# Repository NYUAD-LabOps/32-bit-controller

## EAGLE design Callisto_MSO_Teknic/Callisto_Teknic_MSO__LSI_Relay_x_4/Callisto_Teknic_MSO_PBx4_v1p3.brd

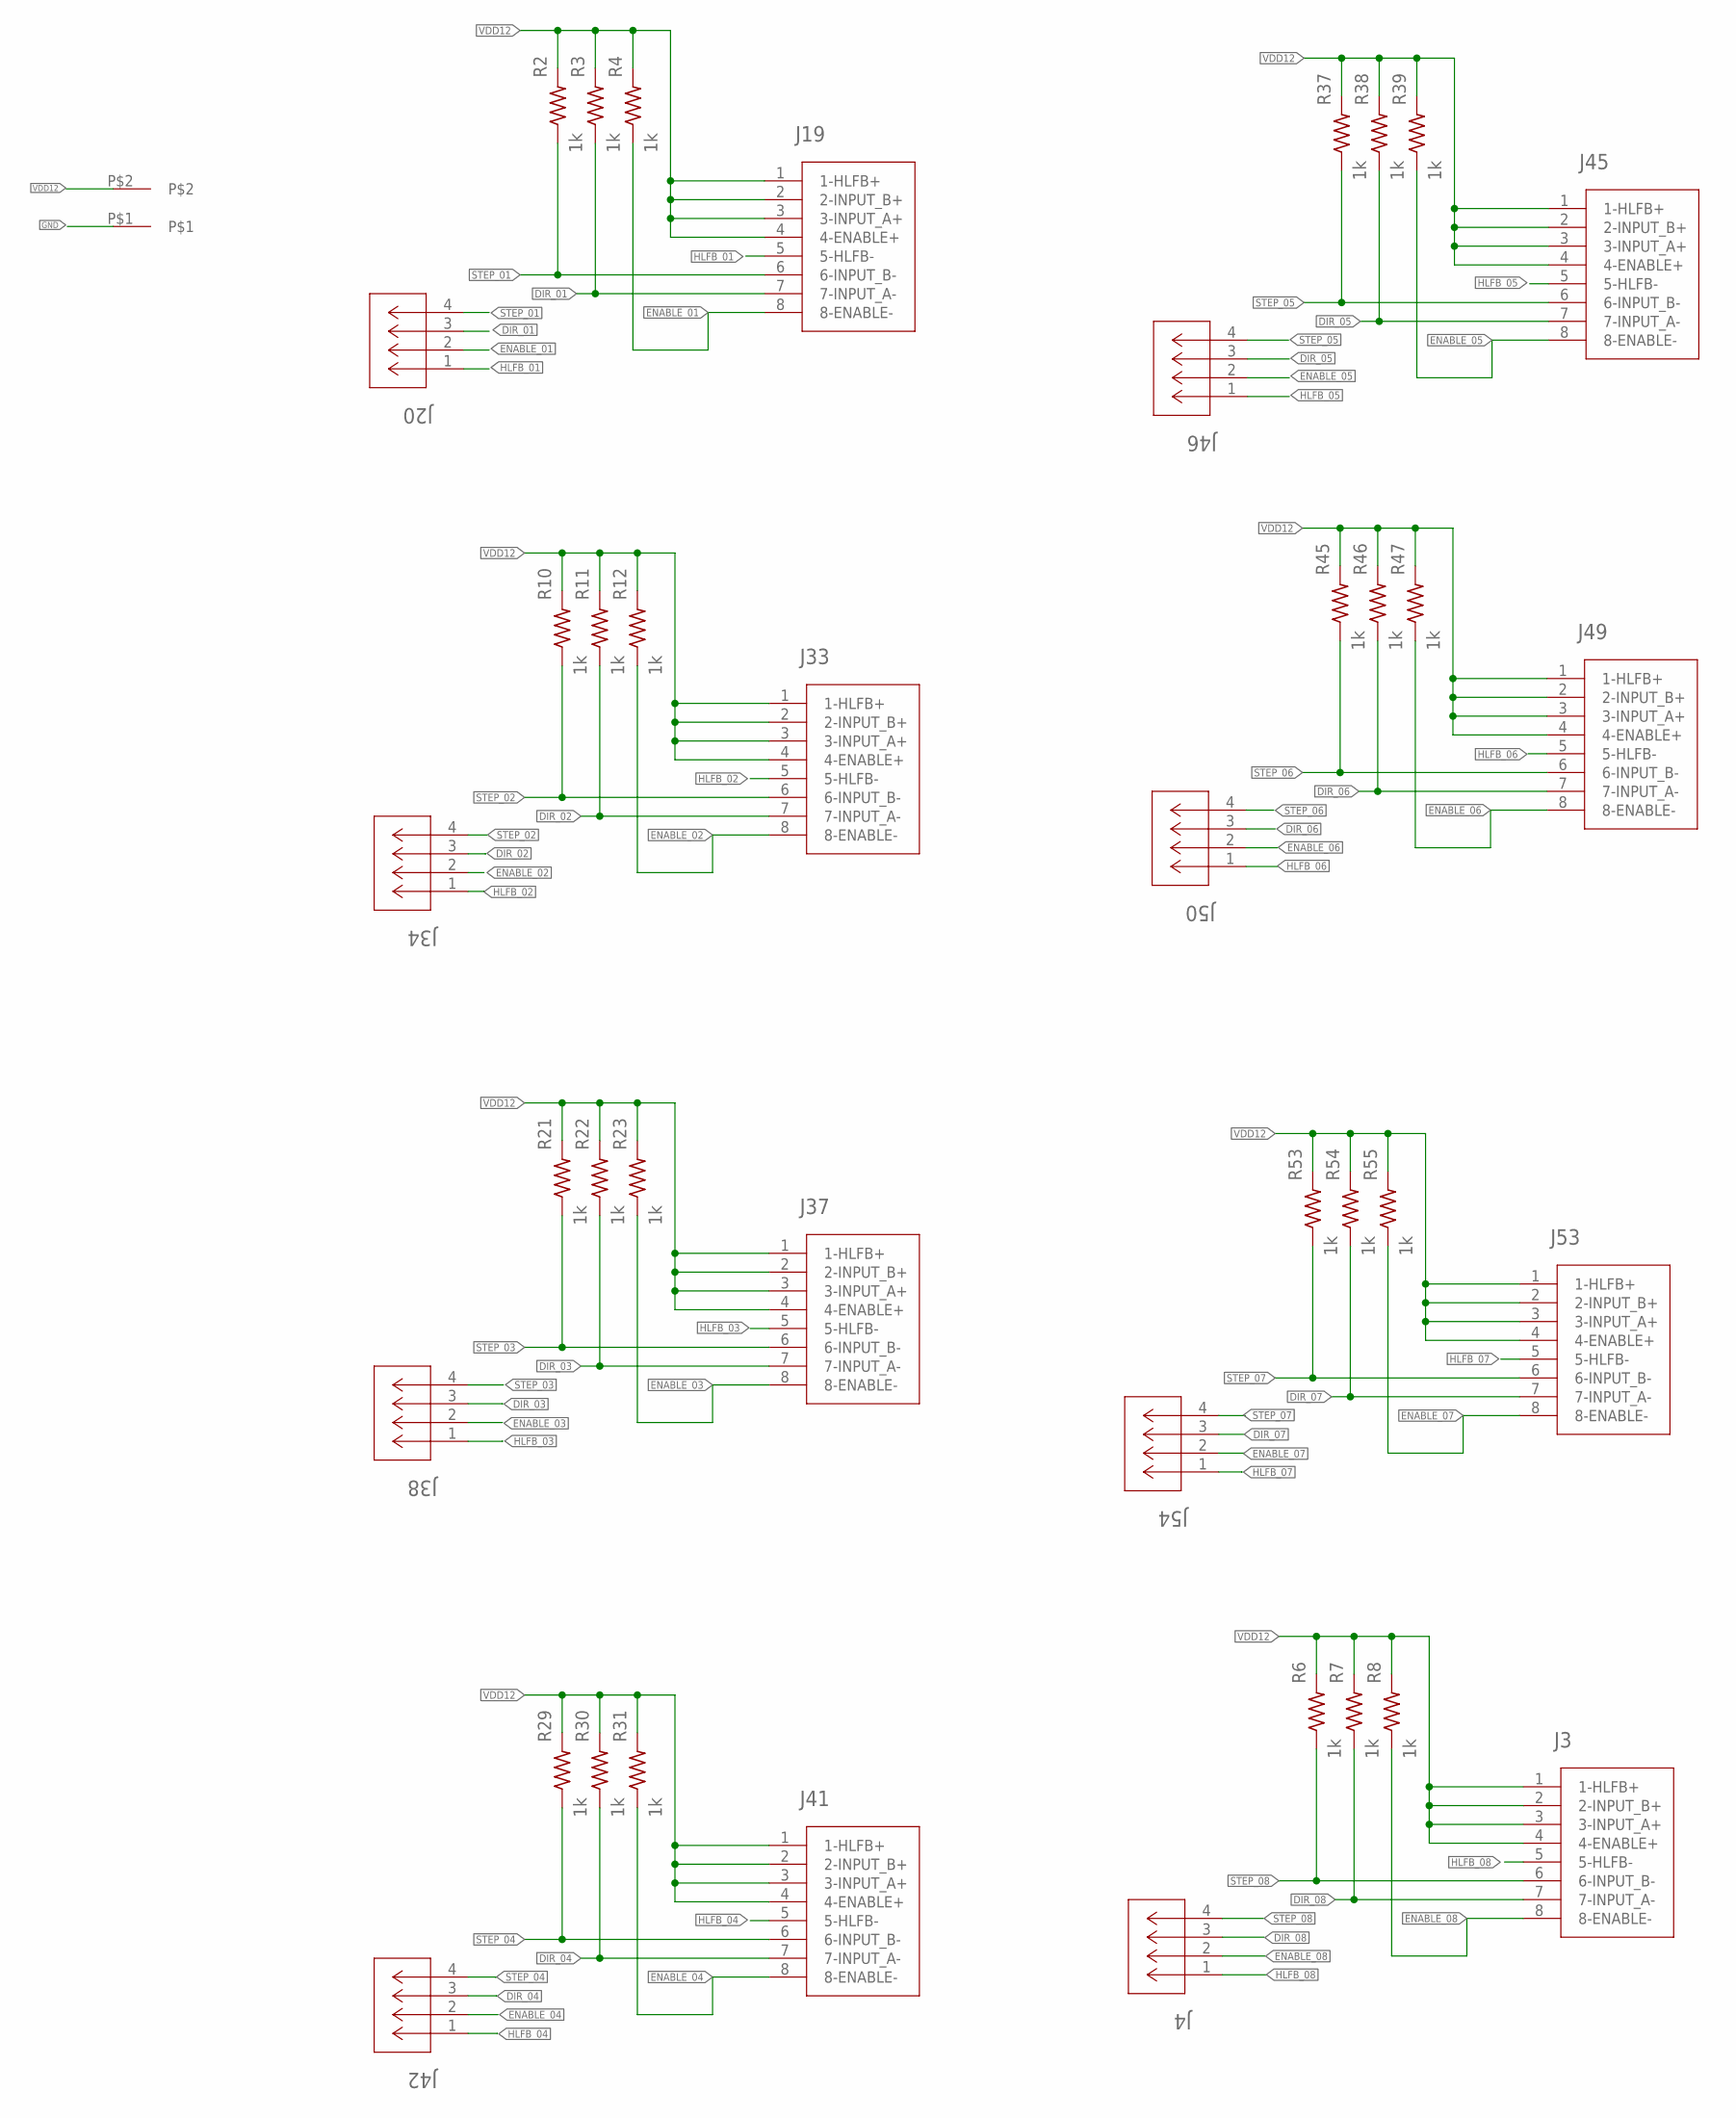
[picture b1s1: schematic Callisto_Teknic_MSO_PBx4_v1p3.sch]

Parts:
J2: 2-pos; 2_3.81MM_PITCH
J3, J19, J33, J37, J41, J45, J49, J53: TEKNIC_8PIN_MOTOR; CON_39281083
J4, J20, J34, J38, J42, J46, J50, J54: CONN_530470410_PICOBLADE_X_4; CON_530470410_MOL
R2, R3, R4, R6, R7, R8, R10, R11, R12, R21, R22, R23, R29, R30, R31, R37, R38, R39, R45, R46, R47, R53, R54, R55: 1k; 0805

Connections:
DIR_01: J19.7 (7-INPUT_A-), J20.3, R3.1
DIR_02: J33.7 (7-INPUT_A-), J34.3, R11.1
DIR_03: J37.7 (7-INPUT_A-), J38.3, R22.1
DIR_04: J41.7 (7-INPUT_A-), J42.3, R30.1
DIR_05: J45.7 (7-INPUT_A-), J46.3, R38.1
DIR_06: J49.7 (7-INPUT_A-), J50.3, R46.1
DIR_07: J53.7 (7-INPUT_A-), J54.3, R54.1
DIR_08: J3.7 (7-INPUT_A-), J4.3, R7.1
ENABLE_01: J19.8 (8-ENABLE-), J20.2, R4.1
ENABLE_02: J33.8 (8-ENABLE-), J34.2, R12.1
ENABLE_03: J37.8 (8-ENABLE-), J38.2, R23.1
ENABLE_04: J41.8 (8-ENABLE-), J42.2, R31.1
ENABLE_05: J45.8 (8-ENABLE-), J46.2, R39.1
ENABLE_06: J49.8 (8-ENABLE-), J50.2, R47.1
ENABLE_07: J53.8 (8-ENABLE-), J54.2, R55.1
ENABLE_08: J3.8 (8-ENABLE-), J4.2, R8.1
GND: J2.P$1
HLFB_01: J19.5 (5-HLFB-), J20.1
HLFB_02: J33.5 (5-HLFB-), J34.1
HLFB_03: J37.5 (5-HLFB-), J38.1
HLFB_04: J41.5 (5-HLFB-), J42.1
HLFB_05: J45.5 (5-HLFB-), J46.1
HLFB_06: J49.5 (5-HLFB-), J50.1
HLFB_07: J53.5 (5-HLFB-), J54.1
HLFB_08: J3.5 (5-HLFB-), J4.1
STEP_01: J19.6 (6-INPUT_B-), J20.4, R2.1
STEP_02: J33.6 (6-INPUT_B-), J34.4, R10.1
STEP_03: J37.6 (6-INPUT_B-), J38.4, R21.1
STEP_04: J41.6 (6-INPUT_B-), J42.4, R29.1
STEP_05: J45.6 (6-INPUT_B-), J46.4, R37.1
STEP_06: J49.6 (6-INPUT_B-), J50.4, R45.1
STEP_07: J53.6 (6-INPUT_B-), J54.4, R53.1
STEP_08: J3.6 (6-INPUT_B-), J4.4, R6.1
VDD12: J2.P$2, J3.1 (1-HLFB+), J3.2 (2-INPUT_B+), J3.3 (3-INPUT_A+), J3.4 (4-ENABLE+), J19.1 (1-HLFB+), J19.2 (2-INPUT_B+), J19.3 (3-INPUT_A+), J19.4 (4-ENABLE+), J33.1 (1-HLFB+), J33.2 (2-INPUT_B+), J33.3 (3-INPUT_A+), J33.4 (4-ENABLE+), J37.1 (1-HLFB+), J37.2 (2-INPUT_B+), J37.3 (3-INPUT_A+), J37.4 (4-ENABLE+), J41.1 (1-HLFB+), J41.2 (2-INPUT_B+), J41.3 (3-INPUT_A+), J41.4 (4-ENABLE+), J45.1 (1-HLFB+), J45.2 (2-INPUT_B+), J45.3 (3-INPUT_A+), J45.4 (4-ENABLE+), J49.1 (1-HLFB+), J49.2 (2-INPUT_B+), J49.3 (3-INPUT_A+), J49.4 (4-ENABLE+), J53.1 (1-HLFB+), J53.2 (2-INPUT_B+), J53.3 (3-INPUT_A+), J53.4 (4-ENABLE+), R2.2, R3.2, R4.2, R6.2, R7.2, R8.2, R10.2, R11.2, R12.2, R21.2, R22.2, R23.2, R29.2, R30.2, R31.2, R37.2, R38.2, R39.2, R45.2, R46.2, R47.2, R53.2, R54.2, R55.2

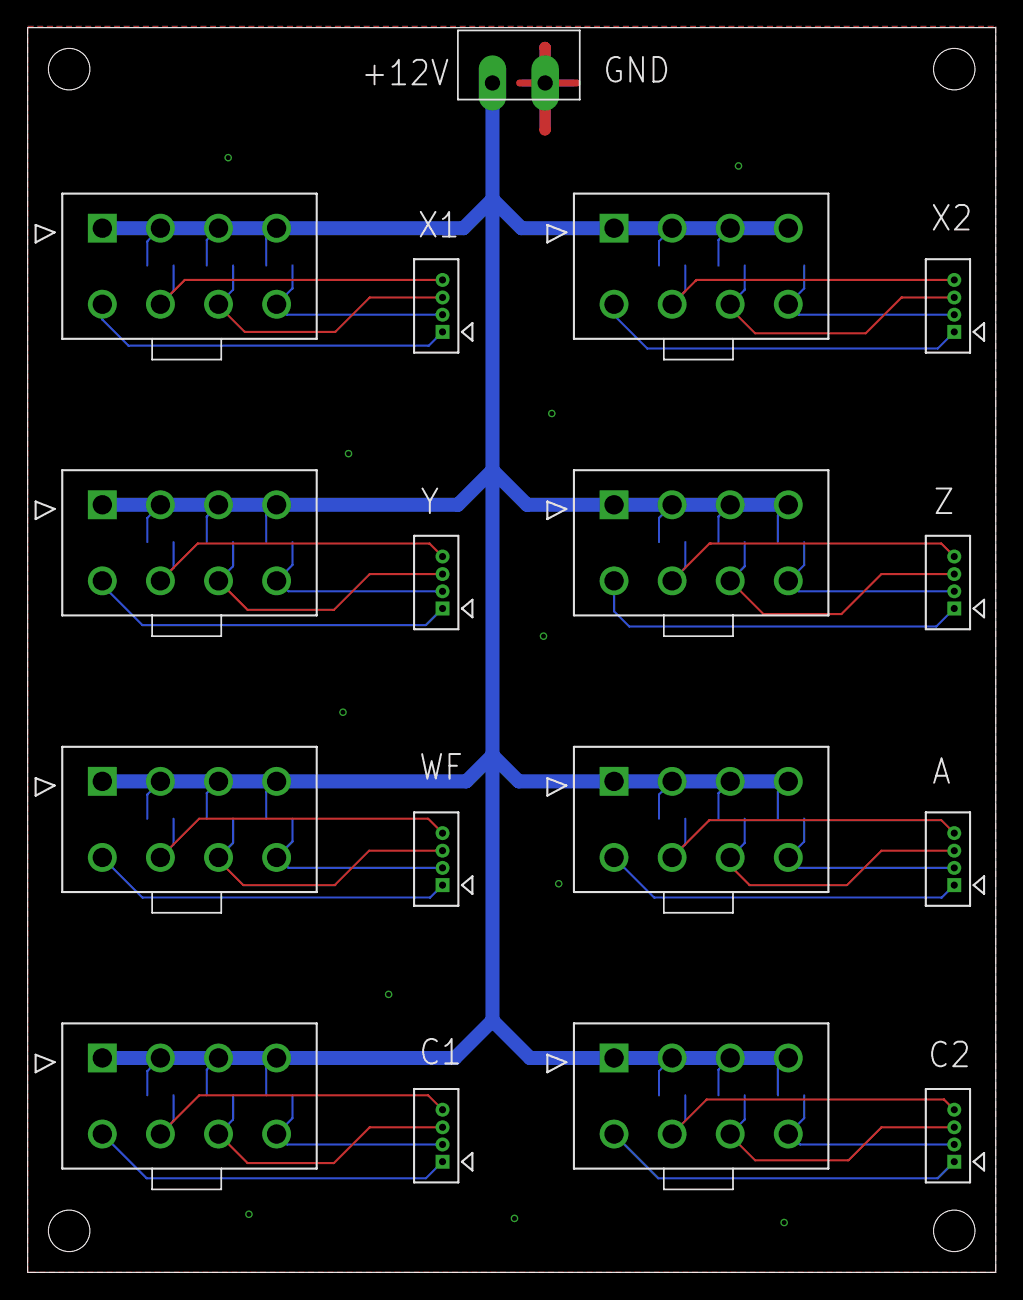
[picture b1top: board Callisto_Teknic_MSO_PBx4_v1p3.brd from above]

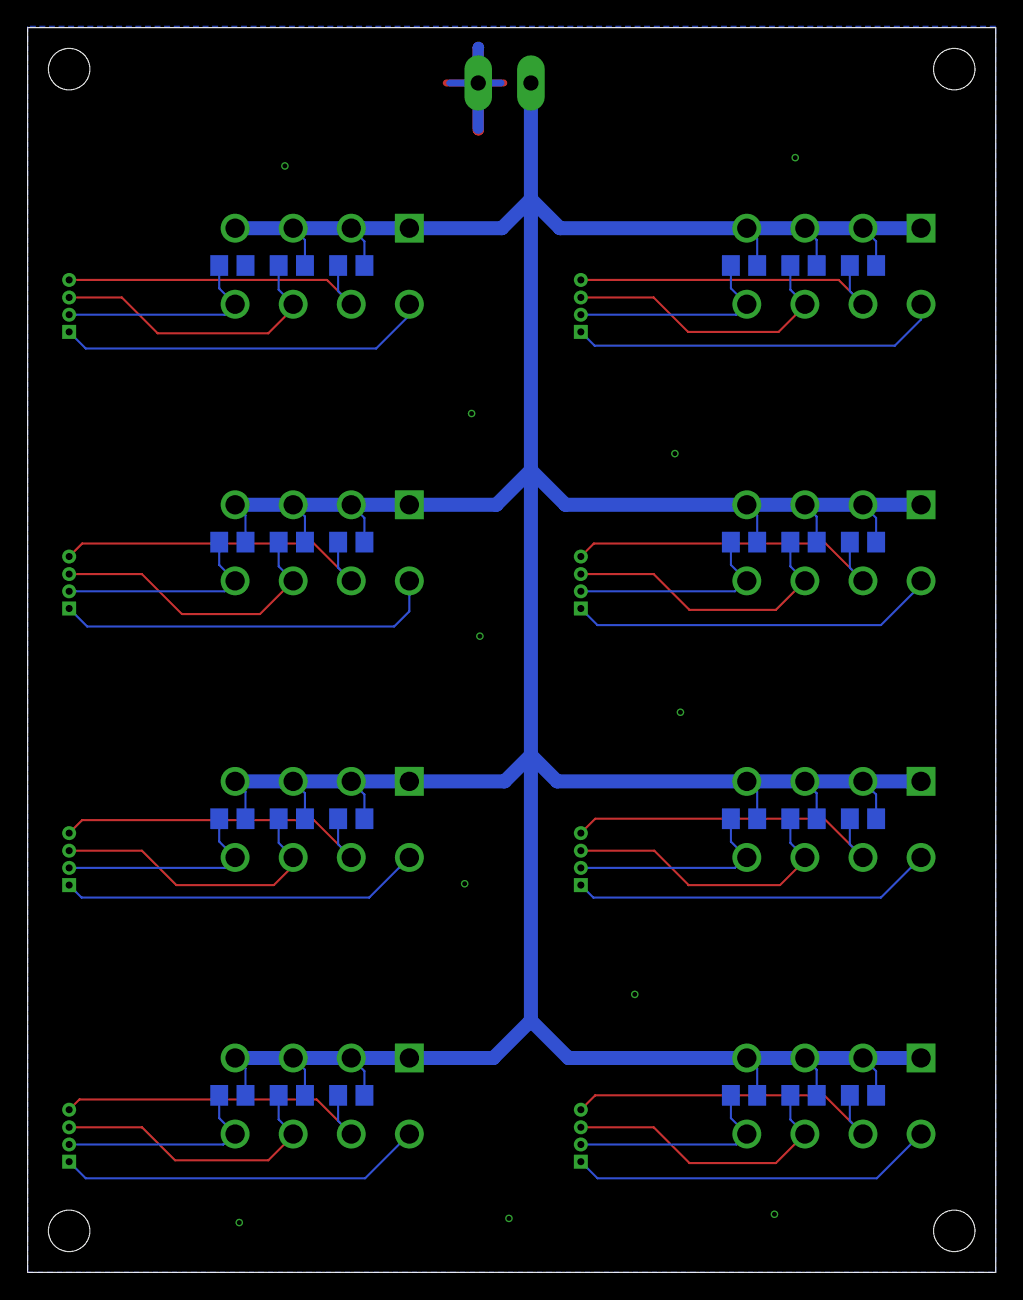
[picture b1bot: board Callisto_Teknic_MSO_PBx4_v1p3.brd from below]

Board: 2 copper layers, 70.0 x 90.0 mm, 41 parts (24 on the bottom side), 33 nets.

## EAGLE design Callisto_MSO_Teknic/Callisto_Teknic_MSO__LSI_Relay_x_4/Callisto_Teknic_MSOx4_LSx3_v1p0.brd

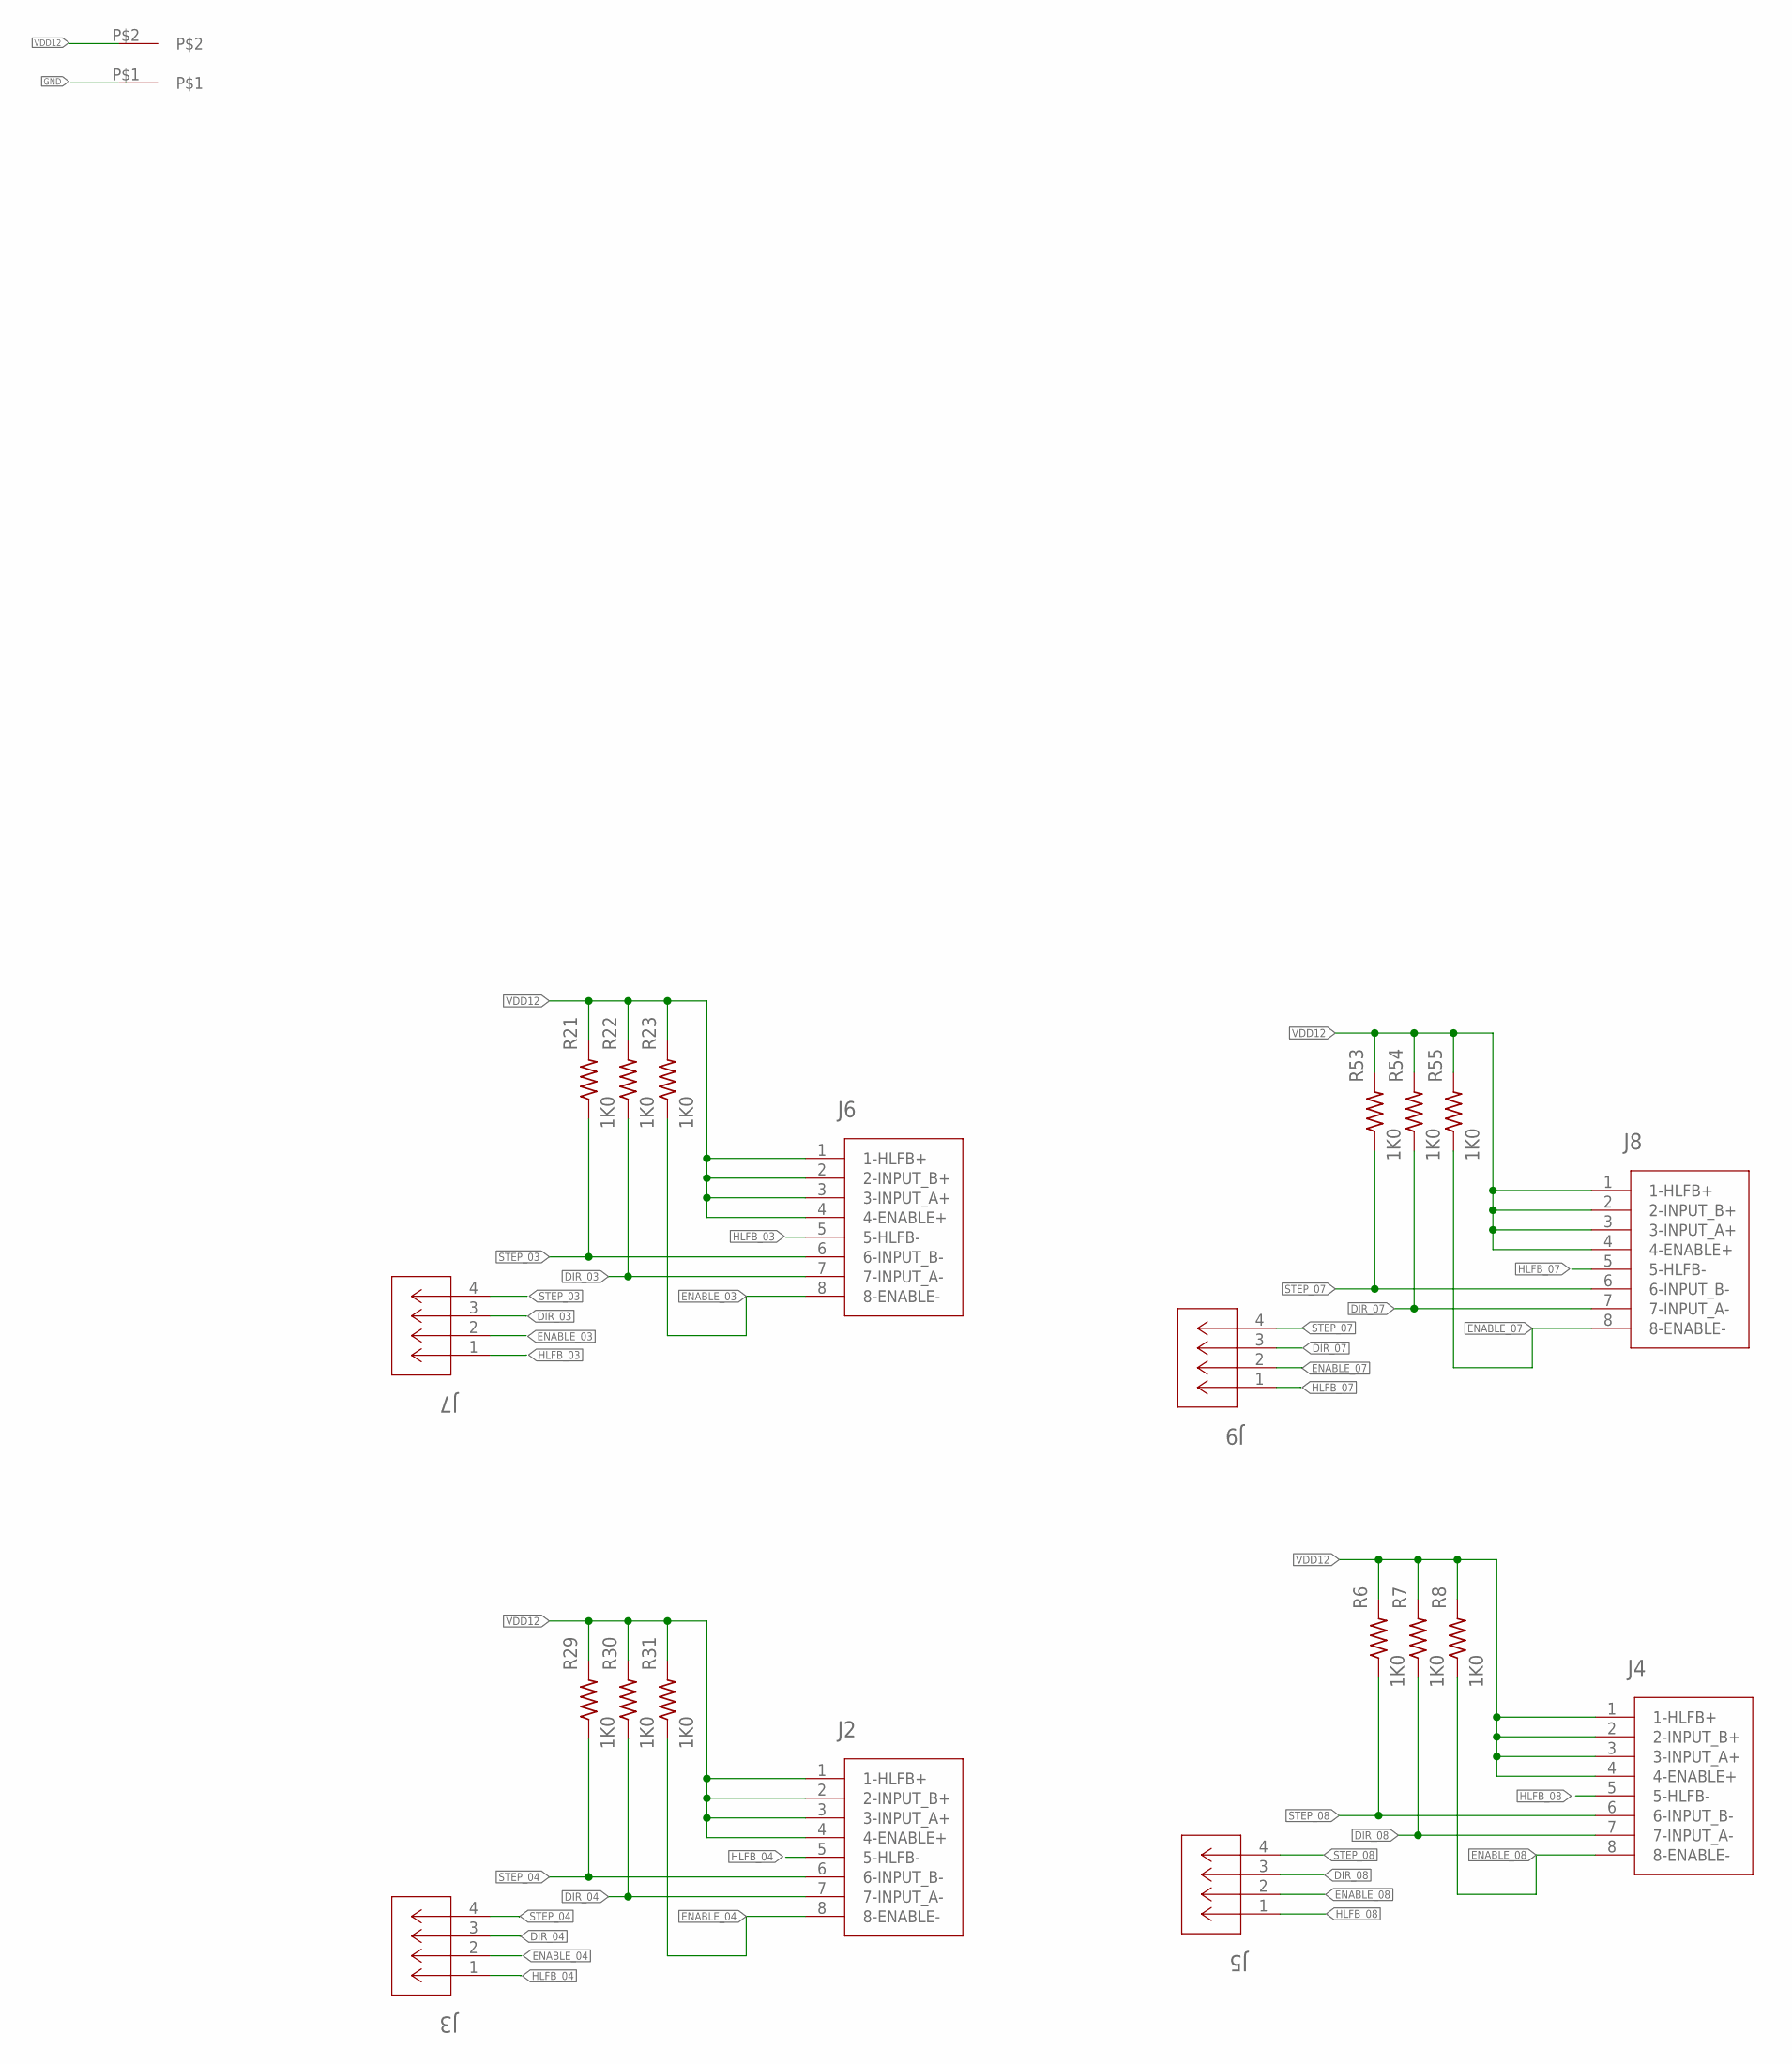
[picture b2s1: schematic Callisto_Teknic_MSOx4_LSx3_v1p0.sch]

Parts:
J1: 2-pos; 2_3.81MM_PITCH
J2, J4, J6, J8: TEKNIC_8PIN_MOTOR; CON_39281083
J3, J5, J7, J9: CONN_530470410_PICOBLADE_X_4; CON_530470410_MOL
R6, R7, R8, R21, R22, R23, R29, R30, R31, R53, R54, R55: 1K0; 0402

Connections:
DIR_03: J6.7 (7-INPUT_A-), J7.3, R22.1
DIR_04: J2.7 (7-INPUT_A-), J3.3, R30.1
DIR_07: J8.7 (7-INPUT_A-), J9.3, R54.1
DIR_08: J4.7 (7-INPUT_A-), J5.3, R7.1
ENABLE_03: J6.8 (8-ENABLE-), J7.2, R23.1
ENABLE_04: J2.8 (8-ENABLE-), J3.2, R31.1
ENABLE_07: J8.8 (8-ENABLE-), J9.2, R55.1
ENABLE_08: J4.8 (8-ENABLE-), J5.2, R8.1
GND: J1.P$1
HLFB_03: J6.5 (5-HLFB-), J7.1
HLFB_04: J2.5 (5-HLFB-), J3.1
HLFB_07: J8.5 (5-HLFB-), J9.1
HLFB_08: J4.5 (5-HLFB-), J5.1
STEP_03: J6.6 (6-INPUT_B-), J7.4, R21.1
STEP_04: J2.6 (6-INPUT_B-), J3.4, R29.1
STEP_07: J8.6 (6-INPUT_B-), J9.4, R53.1
STEP_08: J4.6 (6-INPUT_B-), J5.4, R6.1
VDD12: J1.P$2, J2.1 (1-HLFB+), J2.2 (2-INPUT_B+), J2.3 (3-INPUT_A+), J2.4 (4-ENABLE+), J4.1 (1-HLFB+), J4.2 (2-INPUT_B+), J4.3 (3-INPUT_A+), J4.4 (4-ENABLE+), J6.1 (1-HLFB+), J6.2 (2-INPUT_B+), J6.3 (3-INPUT_A+), J6.4 (4-ENABLE+), J8.1 (1-HLFB+), J8.2 (2-INPUT_B+), J8.3 (3-INPUT_A+), J8.4 (4-ENABLE+), R6.2, R7.2, R8.2, R21.2, R22.2, R23.2, R29.2, R30.2, R31.2, R53.2, R54.2, R55.2

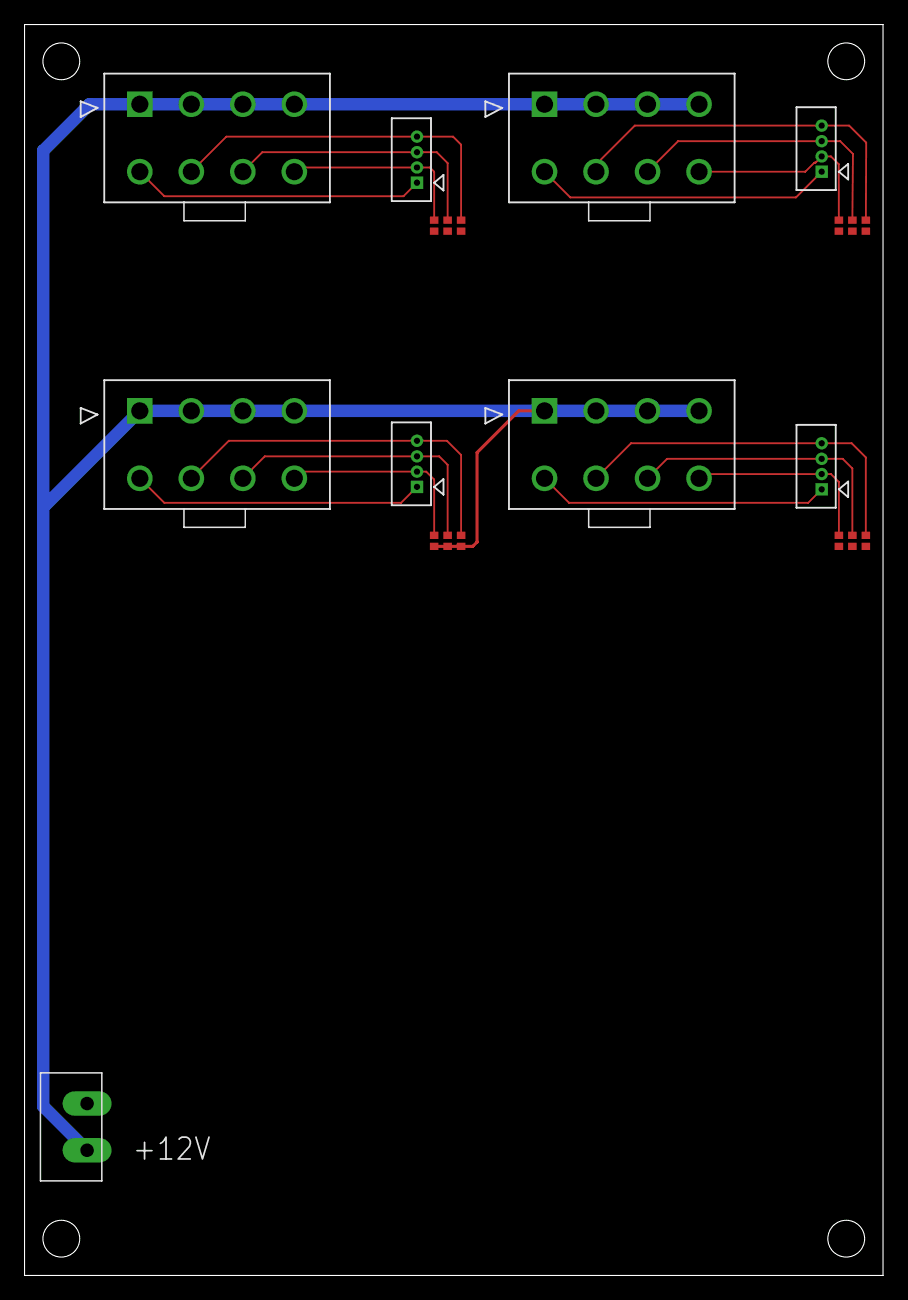
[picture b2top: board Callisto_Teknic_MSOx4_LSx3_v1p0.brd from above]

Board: 2 copper layers, 70.0 x 102.0 mm, 21 parts (0 on the bottom side), 17 nets.

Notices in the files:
parts and their libraries:
COPYRIGHT: Copyright (C) 2022 Ultra Librarian. All rights reserved.
COPYRIGHT: Copyright (C) 2018 Accelerated Designs. All rights reserved
